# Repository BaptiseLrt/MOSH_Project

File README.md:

# MOSH_Project
5ISS_MOSH_LESSONS

# Mini-Project

# Piste bleue

Objectifs:

1) Réaliser un prototype rapide sur breadboard qui permet d'envoyer les données du capteur de gaz sur The Thing Networks (https://www.thethingsnetwork.org/)

2) Réalisation du shield grâce à KiCAD

(fait en cours)

3) Gestion d’une interruption sur le capteur de gaz signalant la présence d’un danger

On souhaite réaliser une interruption analogique sur le pin 2 lorsqu'un danger est detecté. Dans le cadre du tp, nous fixons donc un seuil de dangerosité à 0.7V. 
Sachant que l'entrée analogique du pin 2 considère l'état haut à 0.7 Vcc et l'état bas 0.3 Vcc, nous devons implémenter un comparateur d'intensité qui délivre au moins 0.7Vcc lorsque le capteur de gaz fournit 0.7 V.

Nous avons choisi un montage comparateur non inverseur avec un AOP, 2 résistances et une led qui s'allume lorque l'interruption est levée:

(insérer schéma et calculs voir ipad)

# Piste rouge

On doit réduire la conso d'énergie au maximum 

Avec le montage précédent nous consommons

0.3A au setup et 0.27 A en fonctionnement

sleep mode
power off certains trucs

Après avoir activé le sleep mode lorsqu'aucun danger n'est detecté et en ayant désactivé tous les composants dont nous ne nous servons pas (spi, i2c, etc) on descend à 0.04A (sans le capteur de temperature) et 0.24A avec le capteur.

on peut essayer de ralentir clock arduino

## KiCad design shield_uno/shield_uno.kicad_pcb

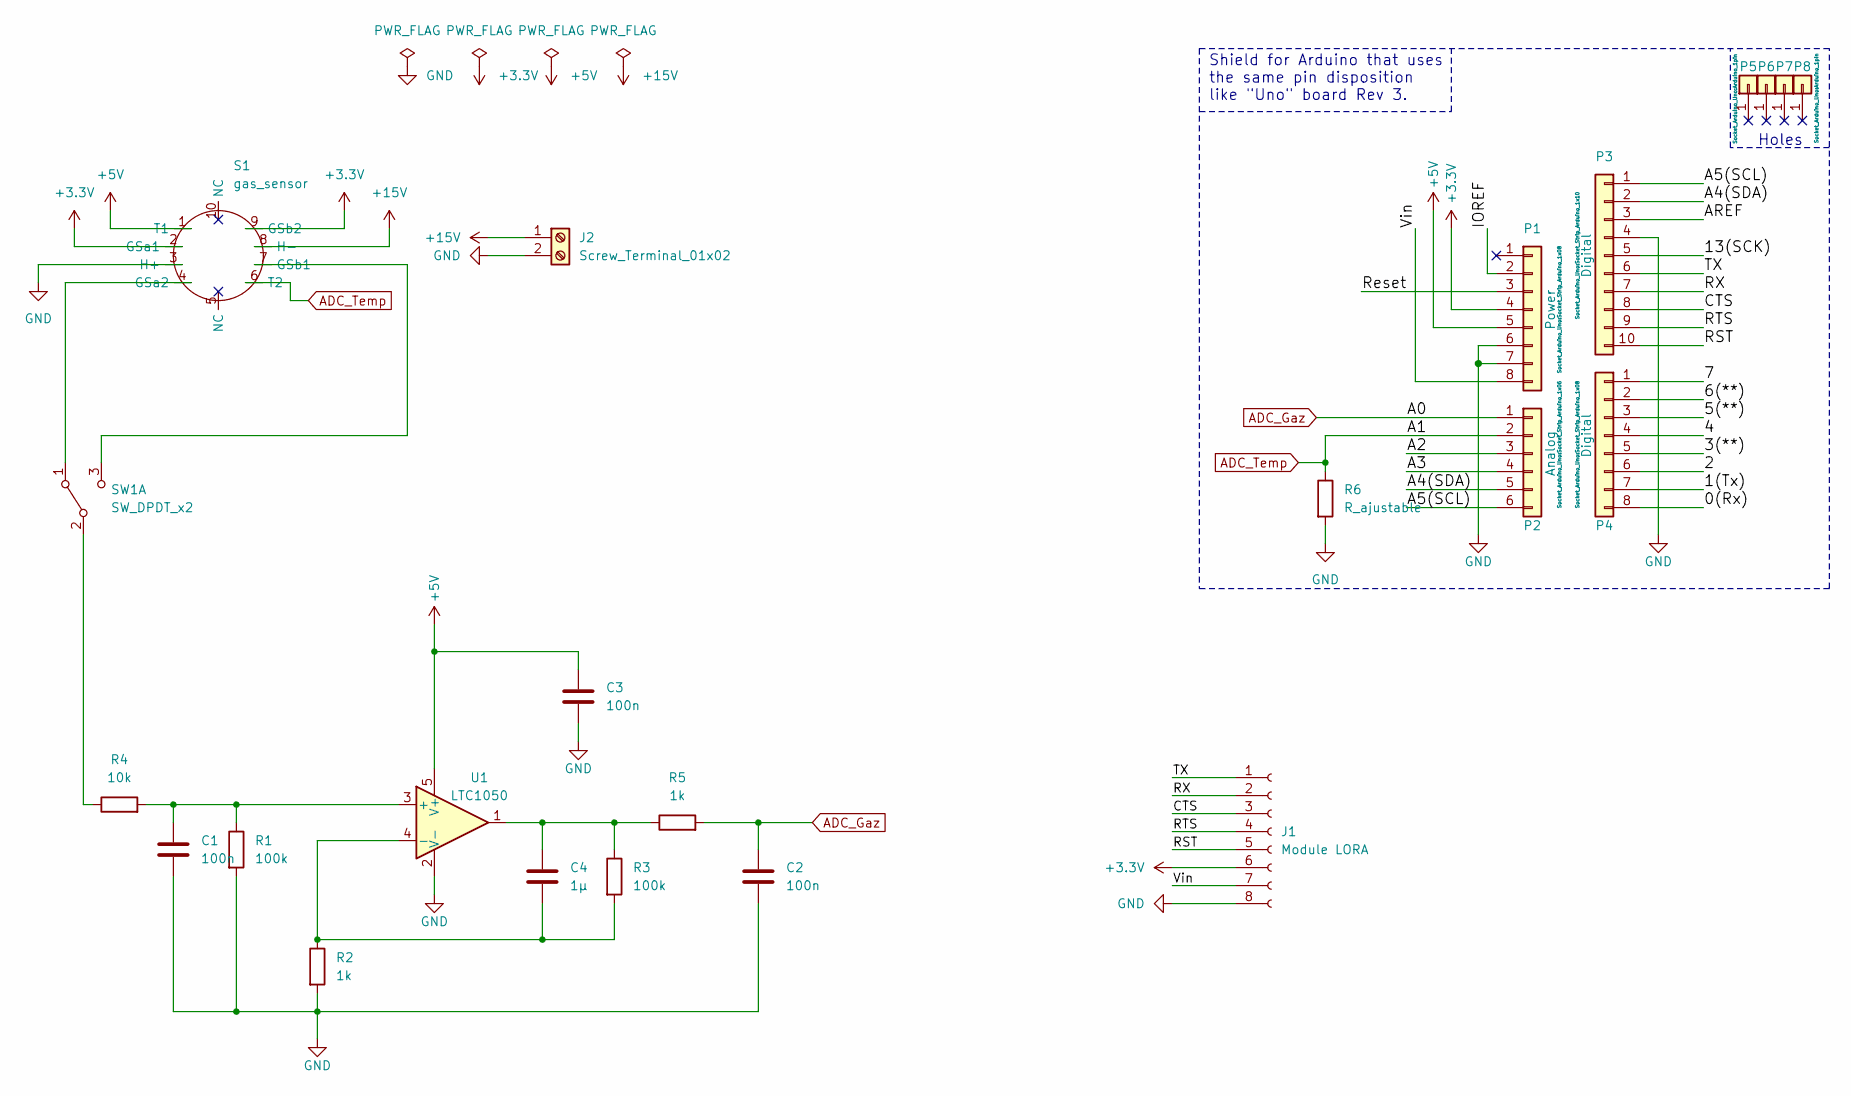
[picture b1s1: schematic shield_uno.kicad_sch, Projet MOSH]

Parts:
C1, C2, C3: 100n; CP_Radial_D5.0mm_P2.50mm
C4: 1µ; CP_Radial_D5.0mm_P2.50mm
J1: Module LORA; PinSocket_1x08_P2.54mm_Vertical
J2: Screw_Terminal_01x02; TerminalBlock_Phoenix_MKDS-1,5-2-5.08_1x02_P5.08mm_Horizont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
P1: Power; Socket_Strip_Arduino_1x08
P2: Analog; Socket_Strip_Arduino_1x06
P3: Digital; Socket_Strip_Arduino_1x10
P4: Digital; Socket_Strip_Arduino_1x08
P5, P6, P7, P8: CONN_01X01; Arduino_1pin
R1, R3: 100k; R_Axial_DIN0204_L3.6mm_D1.6mm_P7.62mm_Horizontal
R2, R5: 1k; R_Axial_DIN0204_L3.6mm_D1.6mm_P7.62mm_Horizontal
R4: 10k; R_Axial_DIN0204_L3.6mm_D1.6mm_P7.62mm_Horizontal
R6: R_ajustable; R_Axial_DIN0204_L3.6mm_D1.6mm_P7.62mm_Horizontal
S1: gas_sensor; TO-5-10_Window
SW1: SW_DPDT_x2; PinHeader_1x03_P2.54mm_Vertical
U1: LTC1050; DIP-6_W7.62mm

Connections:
+3V3: J1.6, P1.4, S1.2 (GSa1), S1.9 (GSb2)
+5V: C3.1, P1.5, S1.1 (T1), U1.5 (V+)
+15V: J2.1, S1.8 (H-)
/0(Rx): P4.8
/1(Tx): P4.7
/2: P4.6
/3(**): P4.5
/4: P4.4
/5(**): P4.3
/6(**): P4.2
/7: P4.1
/13(SCK): P3.5
/A2: P2.3
/A3: P2.4
/A4(SDA): P2.5, P3.2
/A5(SCL): P2.6, P3.1
/AREF: P3.3
/CTS: J1.3, P3.8
/IOREF: P1.2
/RST: J1.5, P3.10
/RTS: J1.4, P3.9
/RX: J1.2, P3.7
/Reset: P1.3
/TX: J1.1, P3.6
/Vin: J1.7, P1.8
ADC_Gaz: C2.1, P2.1, R5.2
ADC_Temp: P2.2, R6.1, S1.6 (T2)
GND: C1.2, C2.2, C3.2, J1.8, J2.2, P1.6, P1.7, P3.4, R1.2, R2.2, R6.2, S1.3 (H+), U1.2 (V-)
unnamed: C4.2, R2.1, R3.2, U1.4 (-)
unnamed: C1.1, R1.1, R4.2, U1.3 (+)
unnamed: R4.1, SW1.2 (B)
unnamed: C4.1, R3.1, R5.1, U1.1
unnamed: S1.4 (GSa2), SW1.1 (A)
unnamed: S1.7 (GSb1), SW1.3 (C)

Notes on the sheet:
Holes
Shield for Arduino that uses the same pin disposition like "Uno" board Rev 3.

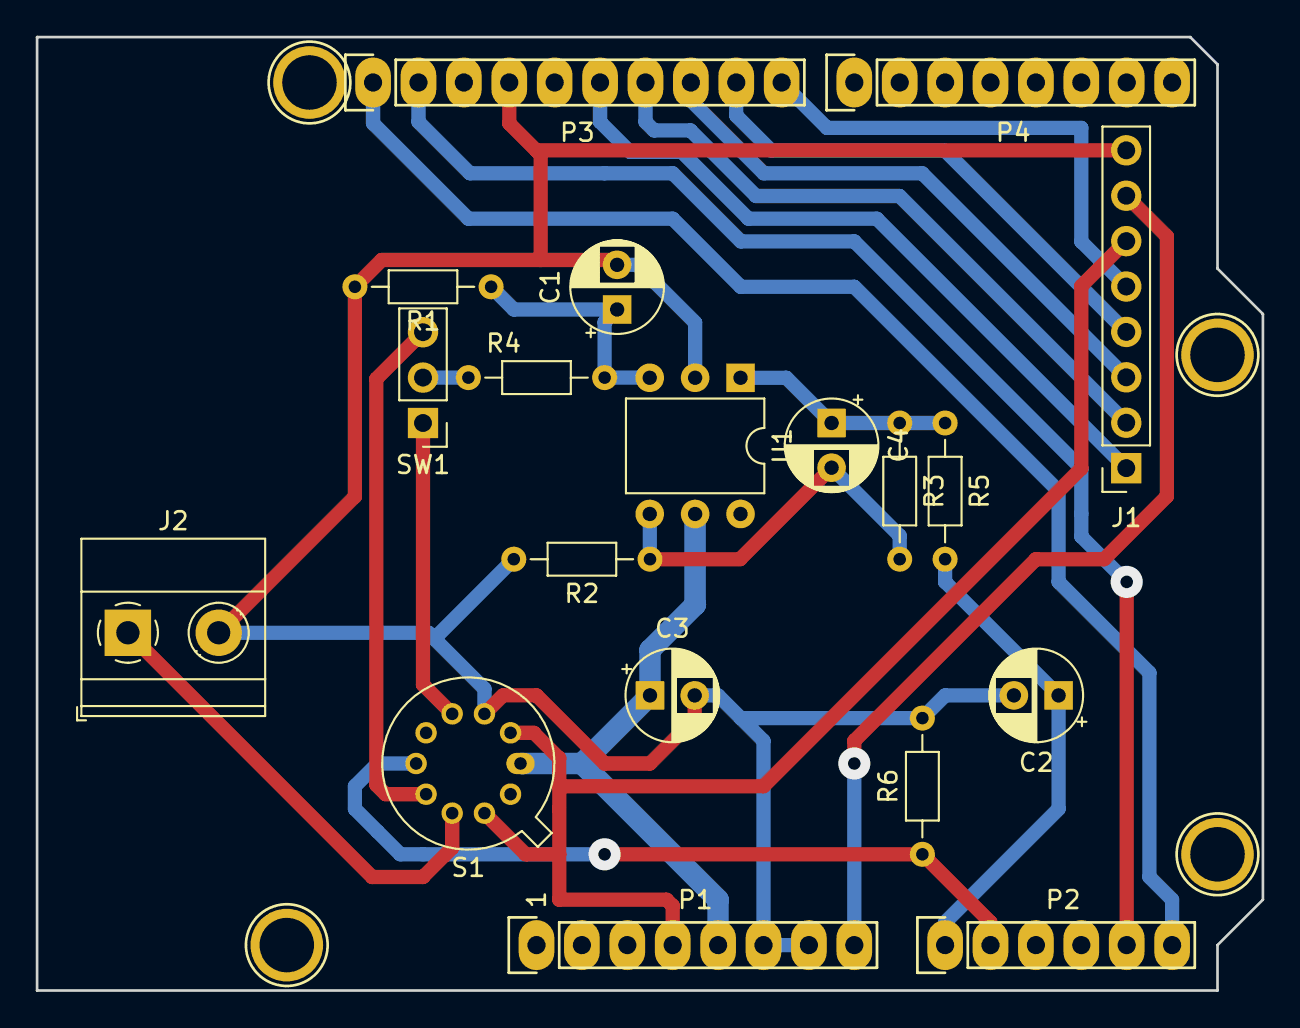
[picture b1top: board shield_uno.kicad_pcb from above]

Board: 2 copper layers, 68.6 x 53.3 mm, 23 parts (0 on the bottom side), 20 nets.

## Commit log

2021-11-17 V00 et V01 => V01 communication avec TTN ok
2021-11-17 Gas interrupt+lora with bytes
    Le feu
2021-11-23 objectives
2021-11-23 Change key and add sleep mode
2021-11-23 Modele avec sleep et interrupt
2021-11-23 Disable some modules in setup
2021-11-23 readme
2022-01-16 Ajout fichiers LTSpice
    Pour le circuit de connection vers l'ADC
2022-01-23 Gaz Sensor Datasheet
2022-01-23 Add Kicad Project
